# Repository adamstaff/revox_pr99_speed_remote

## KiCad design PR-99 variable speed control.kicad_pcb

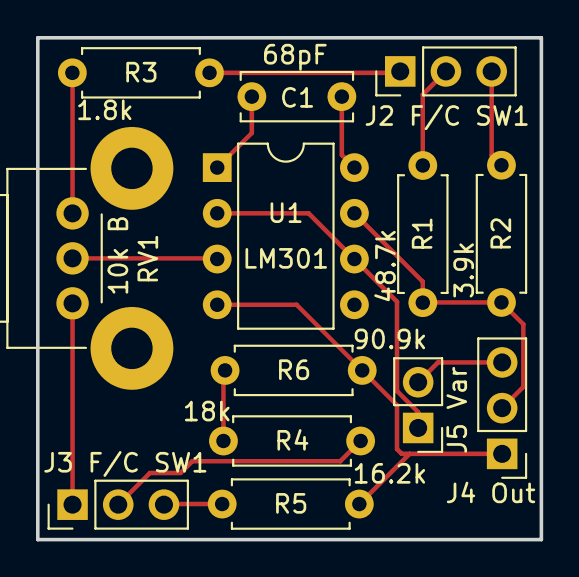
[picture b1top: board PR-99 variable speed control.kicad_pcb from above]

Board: 2 copper layers, 28.0 x 27.9 mm, 13 parts (0 on the bottom side), 15 nets.

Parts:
C1: 68pF; C_Disc_D6.0mm_W2.5mm_P5.00mm
J2 F/C SW1, J3 F/C SW1, J4 Out: Conn_01x03_Socket; PinHeader_1x03_P2.54mm_Vertical
J5 Var: Conn_01x02_Socket; PinHeader_1x02_P2.54mm_Vertical
R1: 48.7k; R_Axial_DIN0207_L6.3mm_D2.5mm_P7.62mm_Horizontal
R2: 3.9k; R_Axial_DIN0207_L6.3mm_D2.5mm_P7.62mm_Horizontal
R3: 1.8k; R_Axial_DIN0207_L6.3mm_D2.5mm_P7.62mm_Horizontal
R4: 18k; R_Axial_DIN0207_L6.3mm_D2.5mm_P7.62mm_Horizontal
R5: 16.2k; R_Axial_DIN0207_L6.3mm_D2.5mm_P7.62mm_Horizontal
R6: 90.9k; R_Axial_DIN0207_L6.3mm_D2.5mm_P7.62mm_Horizontal
RV1: 10k Lin (B); Potentiometer_Bourns_PTV09A-2_Single_Horizontal
U1: LM301; DIP-8_W7.62mm

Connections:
unnamed: J2 F/C SW1.1, R3.2
unnamed: J2 F/C SW1.2, R1.2
unnamed: J2 F/C SW1.3, R2.2
unnamed: J3 F/C SW1.1, RV1.3
unnamed: J3 F/C SW1.2, R4.2
unnamed: J3 F/C SW1.3, R5.2
unnamed: J4 Out.1, R5.1, R6.1, U1.4 (V-)
unnamed: J4 Out.2, R1.1, R2.1, U1.7 (V+)
unnamed: J4 Out.3, J5 Var.2
unnamed: J5 Var.1, U1.2 (-), U1.6
unnamed: R3.1, RV1.1
unnamed: R4.1, R6.2
unnamed: RV1.2, U1.3 (+)
unnamed: C1.1, U1.1 (BAL)
unnamed: C1.2, U1.8 (C/B)
